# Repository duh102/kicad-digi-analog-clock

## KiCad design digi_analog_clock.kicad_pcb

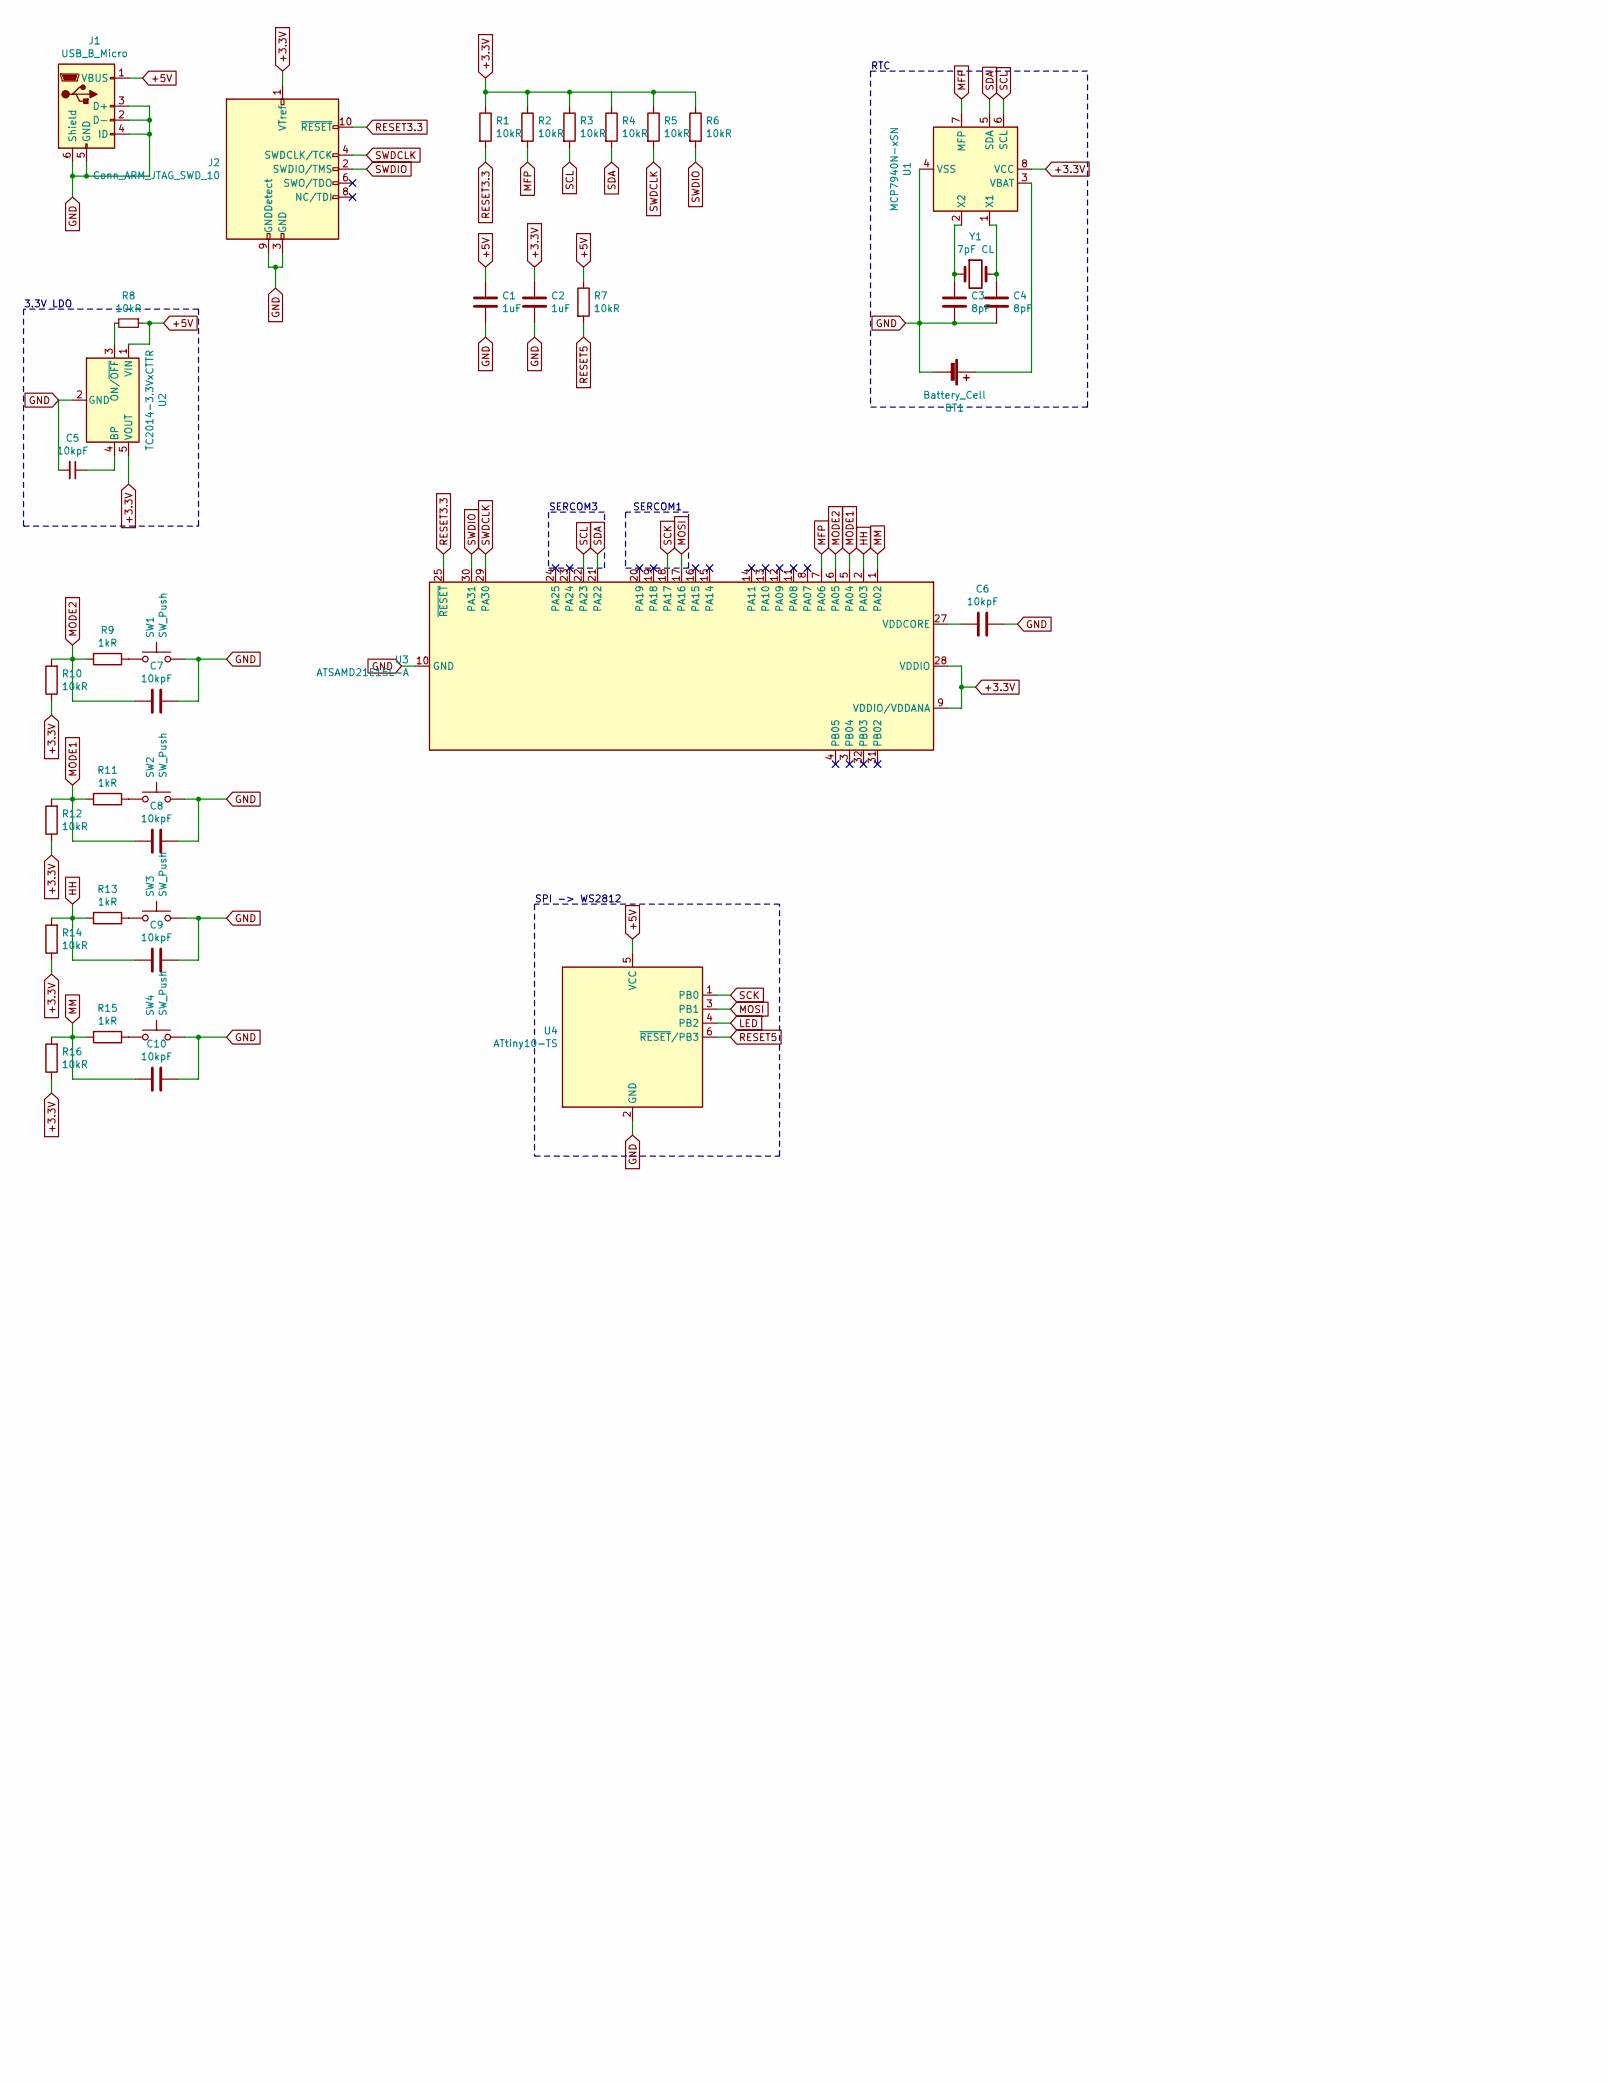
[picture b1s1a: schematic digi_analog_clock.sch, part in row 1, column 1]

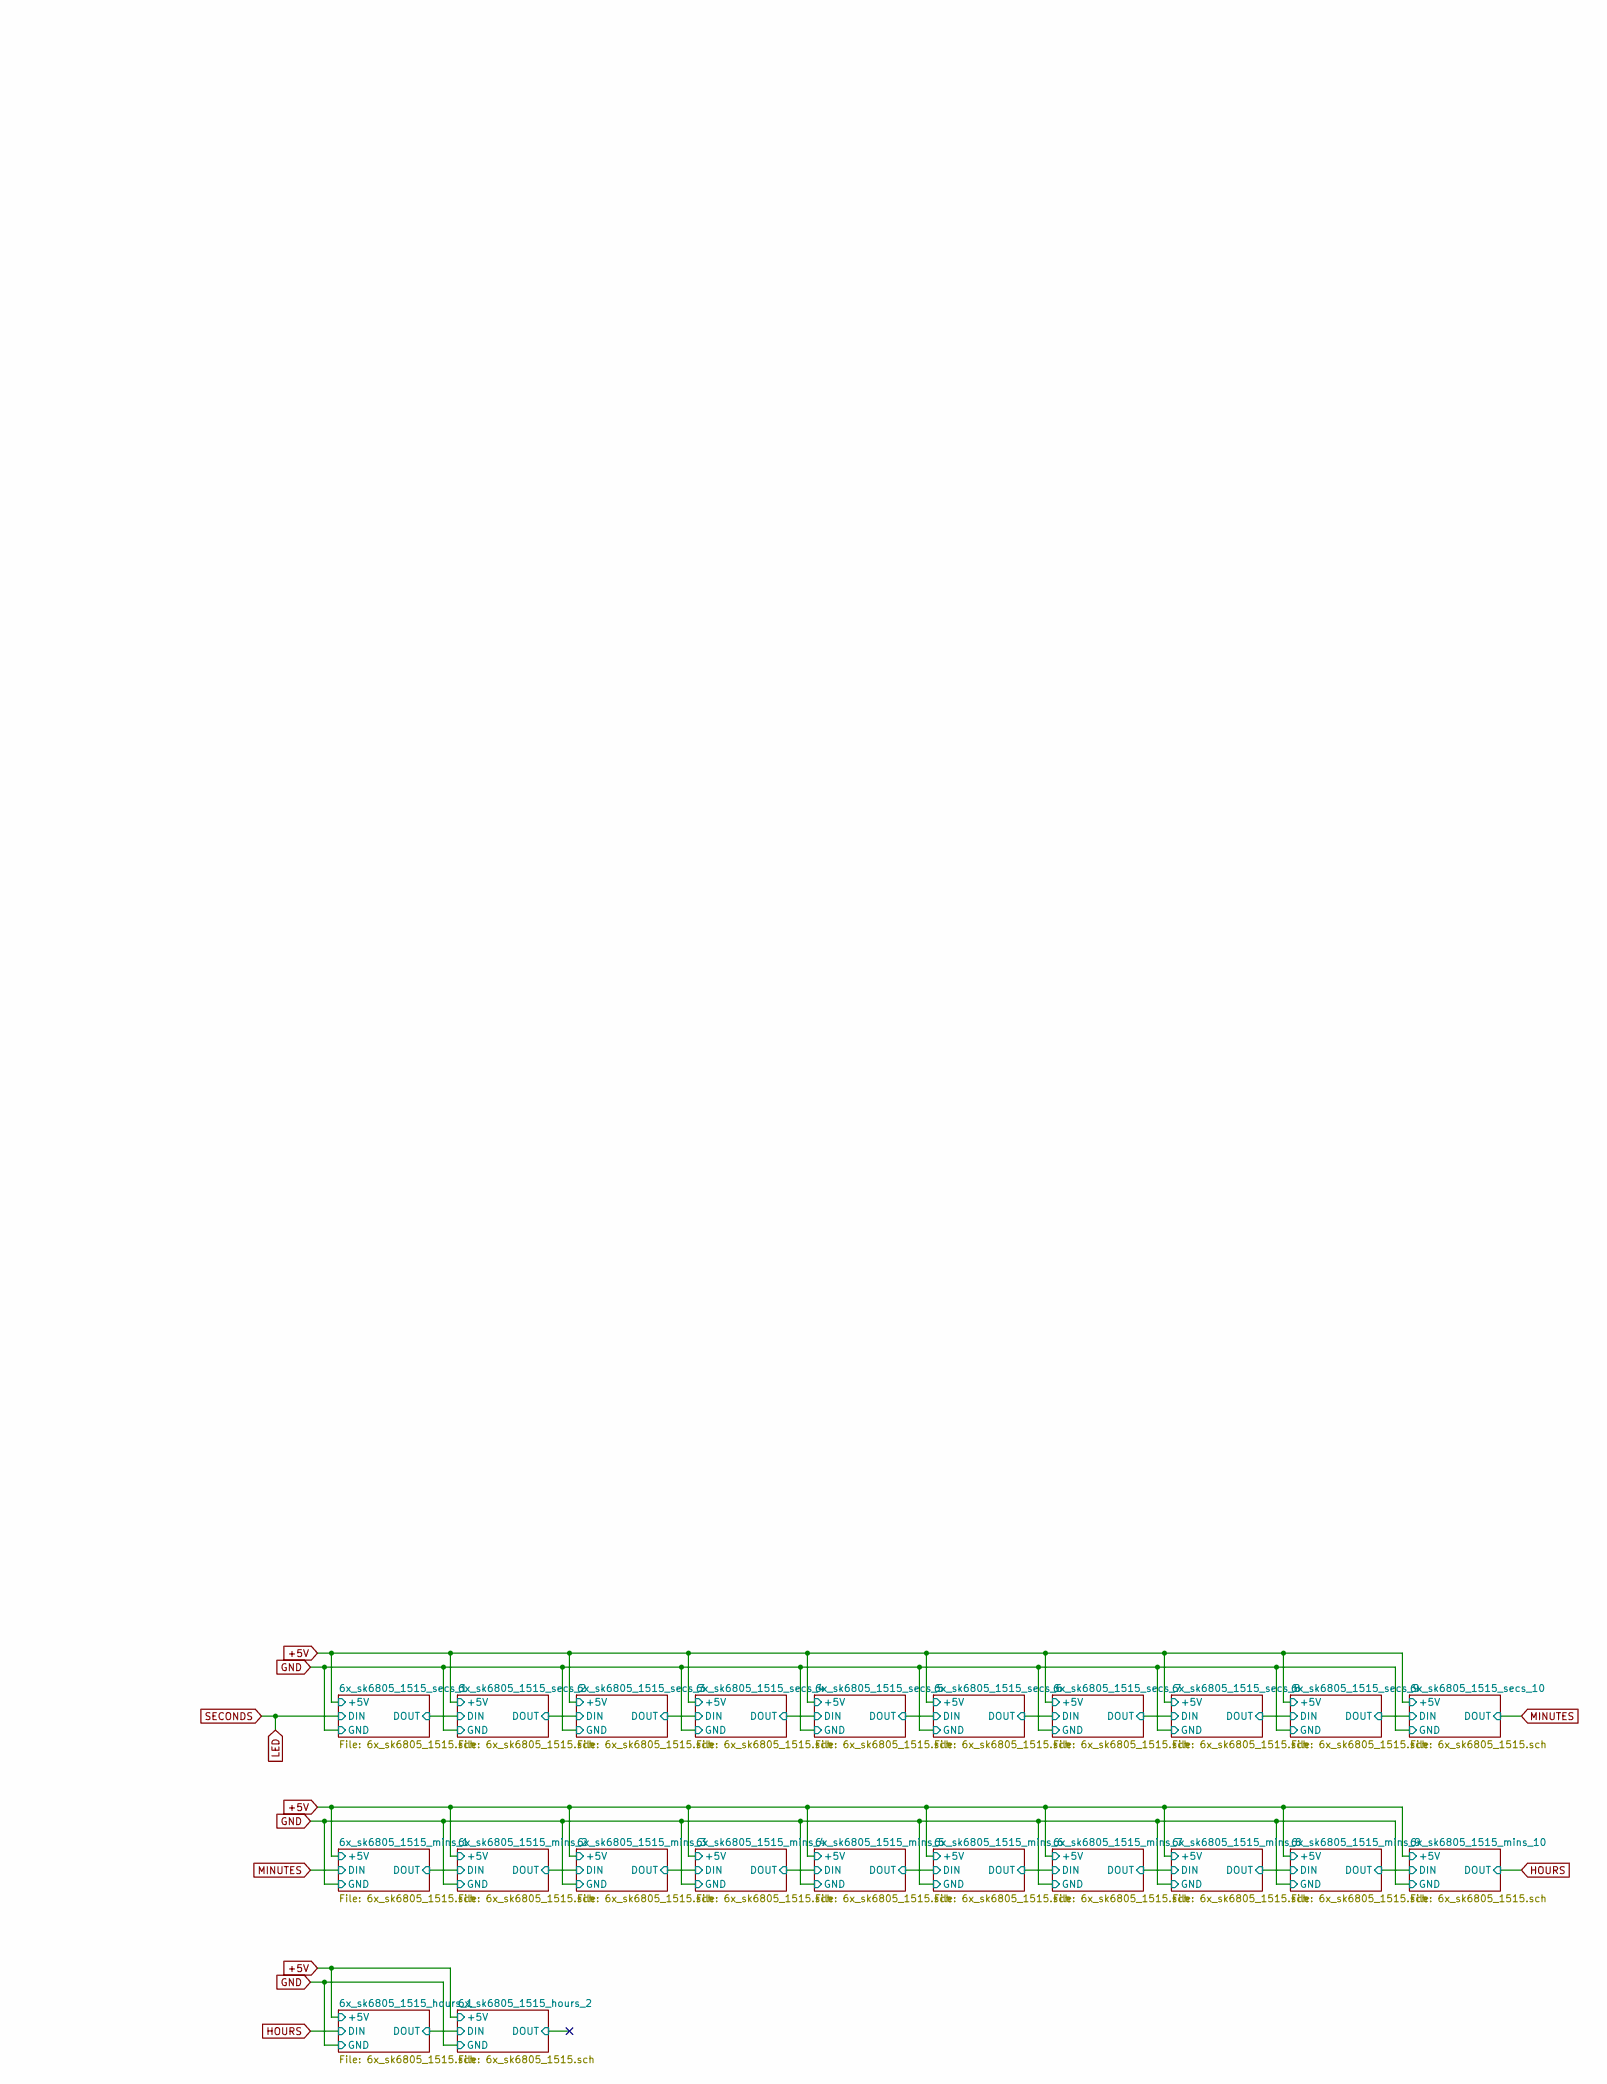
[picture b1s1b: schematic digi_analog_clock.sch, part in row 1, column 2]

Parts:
BT1: Battery_Cell; BatteryHolder_Keystone_3034_1x20mm
C1, C2: 1uF; C_0805_2012Metric
C3, C4: 8pF; C_0805_2012Metric
C5, C6, C7, C8, C9, C10: 10kpF; C_0603_1608Metric
J1: USB_B_Micro; USB_Micro_B_Female_10118194-0001LF
J2: Conn_ARM_JTAG_SWD_10; PinHeader_2x05_P1.27mm_Vertical_SMD
R1, R2, R3, R4, R5, R6, R7, R8, R10, R12, R14, R16: 10kR; R_0805_2012Metric
R9, R11, R13, R15: 1kR; R_0805_2012Metric
SW1, SW2, SW3, SW4: SW_Push; SW_Push_1P1T_Vertical_CK_PTS815
U1: MCP7940N-xSN; SOIC-8_3.9x4.9mm_P1.27mm
U2: TC2014-3.3VxCTTR; SOT-23-5
U3: ATSAMD21E15L-A; TQFP-32_7x7mm_P0.8mm
U4: ATtiny10-TS; SOT-23-6
Y1: 7pF CL; Crystal_SMD_G8-2Pin_3.2x1.5mm

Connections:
+3.3V: C2.1, J2.1 (VTref), R1.1, R2.1, R3.1, R4.1, R5.1, R6.1, R10.1, R12.1, R14.1, R16.1, U1.8 (VCC), U2.5 (VOUT), U3.9 (VDDIO/VDDANA), U3.28 (VDDIO)
+5V: C1.1, J1.1 (VBUS), R7.1, R8.1, U2.1 (VIN), U4.5 (VCC); also elsewhere on the board
GND: BT1.2 (-), C1.2, C2.2, C3.2, C4.1, C5.2, C6.1, C7.1, C8.1, C9.1, C10.1, J1.2 (D-), J1.3 (D+), J1.4 (ID), J1.5 (GND), J1.6 (Shield), J2.3 (GND), J2.5 (GND), J2.9 (GNDDetect), SW1.2, SW2.2, SW3.2, SW4.2, U1.4 (VSS), U2.2 (GND), U3.10 (GND), U3.26 (GND), U4.2 (GND); also elsewhere on the board
HH: C9.2, R13.2, R14.2, U3.2 (PA03)
LED: U4.4 (PB2); also elsewhere on the board
MFP: R2.2, U1.7 (MFP), U3.7 (PA06)
MM: C10.2, R15.2, R16.2, U3.1 (PA02)
MODE1: C8.2, R11.2, R12.2, U3.5 (PA04)
MODE2: C7.2, R9.2, R10.2, U3.6 (PA05)
MOSI: U3.17 (PA16), U4.3 (PB1)
unnamed: BT1.1 (+), U1.3 (VBAT)
unnamed: C3.1, U1.2 (X2), Y1.1
unnamed: C4.2, U1.1 (X1), Y1.2
unnamed: C5.1, U2.4 (BP)
unnamed: C6.2, U3.27 (VDDCORE)
unnamed: R8.2, U2.3 (ON/~OFF~)
unnamed 147: R9.1, SW1.1; also elsewhere on the board
unnamed 148: R11.1, SW2.1; also elsewhere on the board
unnamed 149: R13.1, SW3.1; also elsewhere on the board
unnamed 150: R15.1, SW4.1; also elsewhere on the board
RESET3.3: J2.10 (~RESET~), R1.2, U3.25 (~RESET)
RESET5: R7.2, U4.6 (~RESET~/PB3)
SCK: U3.18 (PA17), U4.1 (PB0)
SCL: R3.2, U1.6 (SCL), U3.22 (PA23)
SDA: R4.2, U1.5 (SDA), U3.21 (PA22)
SWDCLK: J2.4 (SWDCLK/TCK), R5.2, U3.29 (PA30)
SWDIO: J2.2 (SWDIO/TMS), R6.2, U3.30 (PA31)

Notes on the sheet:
SERCOM1
SERCOM3
RTC
SPI -> WS2812
3.3V LDO

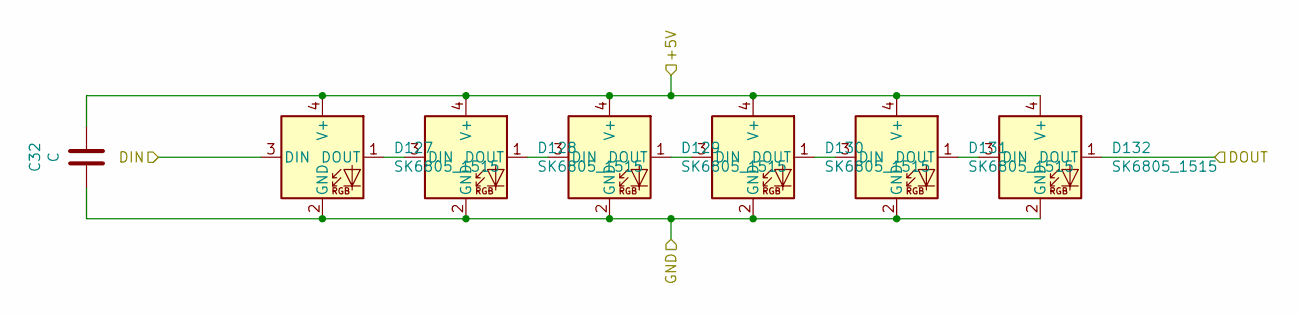
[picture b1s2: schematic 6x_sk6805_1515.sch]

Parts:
C21: C; C_0603_1608Metric
D61, D62, D63, D64, D65, D66: SK6805_1515; LED_SK6805_PLCC4_1.5x1.5mm_P0.65mm

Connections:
+5V: C21.1, D61.4 (V+), D62.4 (V+), D63.4 (V+), D64.4 (V+), D65.4 (V+), D66.4 (V+); also elsewhere on the board
/6x_sk6805_1515_mins_2/DIN: D66.1 (DOUT); also elsewhere on the board
GND: C21.2, D61.2 (GND), D62.2 (GND), D63.2 (GND), D64.2 (GND), D65.2 (GND), D66.2 (GND); also elsewhere on the board
MINUTES: D61.3 (DIN); also elsewhere on the board
unnamed: D61.1 (DOUT), D62.3 (DIN)
unnamed: D62.1 (DOUT), D63.3 (DIN)
unnamed: D63.1 (DOUT), D64.3 (DIN)
unnamed: D64.1 (DOUT), D65.3 (DIN)
unnamed: D65.1 (DOUT), D66.3 (DIN)

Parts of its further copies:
C11, C12, C13, C14, C15, C16, C17, C18, C19, C20, C22, C23, C24, C25, C26, C27, C28, C29, C30, C31, C32: C; C_0603_1608Metric
D1, D2, D3, D4, D5, D6, D7, D8, D9, D10, D11, D12, D13, D14, D15, D16, D17, D18, D19, D20, D21, D22, D23, D24, D25, D26, D27, D28, D29, D30, D31, D32, D33, D34, D35, D36, D37, D38, D39, D40, D41, D42, D43, D44, D45, D46, D47, D48, D49, D50, D51, D52, D53, D54, D55, D56, D57, D58, D59, D60, D67, D68, D69, D70, D71, D72, D73, D74, D75, D76, D77, D78, D79, D80, D81, D82, D83, D84, D85, D86, D87, D88, D89, D90, D91, D92, D93, D94, D95, D96, D97, D98, D99, D100, D101, D102, D103, D104, D105, D106, D107, D108, D109, D110, D111, D112, D113, D114, D115, D116, D117, D118, D119, D120, D121, D122, D123, D124, D125, D126, D127, D128, D129, D130, D131, D132: SK6805_1515; LED_SK6805_PLCC4_1.5x1.5mm_P0.65mm

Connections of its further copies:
+5V: C11.1, C12.1, C13.1, C14.1, C15.1, C16.1, C17.1, C18.1, C19.1, C20.1, C22.1, C23.1, C24.1, C25.1, C26.1, C27.1, C28.1, C29.1, C30.1, C31.1, C32.1, D1.4 (V+), D2.4 (V+), D3.4 (V+), D4.4 (V+), D5.4 (V+), D6.4 (V+), D7.4 (V+), D8.4 (V+), D9.4 (V+), D10.4 (V+), D11.4 (V+), D12.4 (V+), D13.4 (V+), D14.4 (V+), D15.4 (V+), D16.4 (V+), D17.4 (V+), D18.4 (V+), D19.4 (V+), D20.4 (V+), D21.4 (V+), D22.4 (V+), D23.4 (V+), D24.4 (V+), D25.4 (V+), D26.4 (V+), D27.4 (V+), D28.4 (V+), D29.4 (V+), D30.4 (V+), D31.4 (V+), D32.4 (V+), D33.4 (V+), D34.4 (V+), D35.4 (V+), D36.4 (V+), D37.4 (V+), D38.4 (V+), D39.4 (V+), D40.4 (V+), D41.4 (V+), D42.4 (V+), D43.4 (V+), D44.4 (V+), D45.4 (V+), D46.4 (V+), D47.4 (V+), D48.4 (V+), D49.4 (V+), D50.4 (V+), D51.4 (V+), D52.4 (V+), D53.4 (V+), D54.4 (V+), D55.4 (V+), D56.4 (V+), D57.4 (V+), D58.4 (V+), D59.4 (V+), D60.4 (V+), D67.4 (V+), D68.4 (V+), D69.4 (V+), D70.4 (V+), D71.4 (V+), D72.4 (V+), D73.4 (V+), D74.4 (V+), D75.4 (V+), D76.4 (V+), D77.4 (V+), D78.4 (V+), D79.4 (V+), D80.4 (V+), D81.4 (V+), D82.4 (V+), D83.4 (V+), D84.4 (V+), D85.4 (V+), D86.4 (V+), D87.4 (V+), D88.4 (V+), D89.4 (V+), D90.4 (V+), D91.4 (V+), D92.4 (V+), D93.4 (V+), D94.4 (V+), D95.4 (V+), D96.4 (V+), D97.4 (V+), D98.4 (V+), D99.4 (V+), D100.4 (V+), D101.4 (V+), D102.4 (V+), D103.4 (V+), D104.4 (V+), D105.4 (V+), D106.4 (V+), D107.4 (V+), D108.4 (V+), D109.4 (V+), D110.4 (V+), D111.4 (V+), D112.4 (V+), D113.4 (V+), D114.4 (V+), D115.4 (V+), D116.4 (V+), D117.4 (V+), D118.4 (V+), D119.4 (V+), D120.4 (V+), D121.4 (V+), D122.4 (V+), D123.4 (V+), D124.4 (V+), D125.4 (V+), D126.4 (V+), D127.4 (V+), D128.4 (V+), D129.4 (V+), D130.4 (V+), D131.4 (V+), D132.4 (V+); also elsewhere on the board
/6x_sk6805_1515_hours_2/DIN: D126.1 (DOUT), D127.3 (DIN)
/6x_sk6805_1515_mins_2/DIN: D67.3 (DIN); also elsewhere on the board
/6x_sk6805_1515_mins_3/DIN: D72.1 (DOUT), D73.3 (DIN)
/6x_sk6805_1515_mins_4/DIN: D78.1 (DOUT), D79.3 (DIN)
/6x_sk6805_1515_mins_5/DIN: D84.1 (DOUT), D85.3 (DIN)
/6x_sk6805_1515_mins_6/DIN: D90.1 (DOUT), D91.3 (DIN)
/6x_sk6805_1515_mins_7/DIN: D96.1 (DOUT), D97.3 (DIN)
/6x_sk6805_1515_mins_8/DIN: D102.1 (DOUT), D103.3 (DIN)
/6x_sk6805_1515_mins_9/DIN: D108.1 (DOUT), D109.3 (DIN)
/6x_sk6805_1515_mins_10/DIN: D114.1 (DOUT), D115.3 (DIN)
/6x_sk6805_1515_secs_2/DIN: D6.1 (DOUT), D7.3 (DIN)
/6x_sk6805_1515_secs_3/DIN: D12.1 (DOUT), D13.3 (DIN)
/6x_sk6805_1515_secs_4/DIN: D18.1 (DOUT), D19.3 (DIN)
/6x_sk6805_1515_secs_5/DIN: D24.1 (DOUT), D25.3 (DIN)
/6x_sk6805_1515_secs_6/DIN: D30.1 (DOUT), D31.3 (DIN)
/6x_sk6805_1515_secs_7/DIN: D36.1 (DOUT), D37.3 (DIN)
/6x_sk6805_1515_secs_8/DIN: D42.1 (DOUT), D43.3 (DIN)
/6x_sk6805_1515_secs_9/DIN: D48.1 (DOUT), D49.3 (DIN)
/6x_sk6805_1515_secs_10/DIN: D54.1 (DOUT), D55.3 (DIN)
GND: C11.2, C12.2, C13.2, C14.2, C15.2, C16.2, C17.2, C18.2, C19.2, C20.2, C22.2, C23.2, C24.2, C25.2, C26.2, C27.2, C28.2, C29.2, C30.2, C31.2, C32.2, D1.2 (GND), D2.2 (GND), D3.2 (GND), D4.2 (GND), D5.2 (GND), D6.2 (GND), D7.2 (GND), D8.2 (GND), D9.2 (GND), D10.2 (GND), D11.2 (GND), D12.2 (GND), D13.2 (GND), D14.2 (GND), D15.2 (GND), D16.2 (GND), D17.2 (GND), D18.2 (GND), D19.2 (GND), D20.2 (GND), D21.2 (GND), D22.2 (GND), D23.2 (GND), D24.2 (GND), D25.2 (GND), D26.2 (GND), D27.2 (GND), D28.2 (GND), D29.2 (GND), D30.2 (GND), D31.2 (GND), D32.2 (GND), D33.2 (GND), D34.2 (GND), D35.2 (GND), D36.2 (GND), D37.2 (GND), D38.2 (GND), D39.2 (GND), D40.2 (GND), D41.2 (GND), D42.2 (GND), D43.2 (GND), D44.2 (GND), D45.2 (GND), D46.2 (GND), D47.2 (GND), D48.2 (GND), D49.2 (GND), D50.2 (GND), D51.2 (GND), D52.2 (GND), D53.2 (GND), D54.2 (GND), D55.2 (GND), D56.2 (GND), D57.2 (GND), D58.2 (GND), D59.2 (GND), D60.2 (GND), D67.2 (GND), D68.2 (GND), D69.2 (GND), D70.2 (GND), D71.2 (GND), D72.2 (GND), D73.2 (GND), D74.2 (GND), D75.2 (GND), D76.2 (GND), D77.2 (GND), D78.2 (GND), D79.2 (GND), D80.2 (GND), D81.2 (GND), D82.2 (GND), D83.2 (GND), D84.2 (GND), D85.2 (GND), D86.2 (GND), D87.2 (GND), D88.2 (GND), D89.2 (GND), D90.2 (GND), D91.2 (GND), D92.2 (GND), D93.2 (GND), D94.2 (GND), D95.2 (GND), D96.2 (GND), D97.2 (GND), D98.2 (GND), D99.2 (GND), D100.2 (GND), D101.2 (GND), D102.2 (GND), D103.2 (GND), D104.2 (GND), D105.2 (GND), D106.2 (GND), D107.2 (GND), D108.2 (GND), D109.2 (GND), D110.2 (GND), D111.2 (GND), D112.2 (GND), D113.2 (GND), D114.2 (GND), D115.2 (GND), D116.2 (GND), D117.2 (GND), D118.2 (GND), D119.2 (GND), D120.2 (GND), D121.2 (GND), D122.2 (GND), D123.2 (GND), D124.2 (GND), D125.2 (GND), D126.2 (GND), D127.2 (GND), D128.2 (GND), D129.2 (GND), D130.2 (GND), D131.2 (GND), D132.2 (GND); also elsewhere on the board
HOURS: D120.1 (DOUT), D121.3 (DIN)
LED: D1.3 (DIN); also elsewhere on the board
MINUTES: D60.1 (DOUT); also elsewhere on the board
unnamed: D1.1 (DOUT), D2.3 (DIN)
unnamed: D2.1 (DOUT), D3.3 (DIN)
unnamed: D3.1 (DOUT), D4.3 (DIN)
unnamed: D4.1 (DOUT), D5.3 (DIN)
unnamed: D5.1 (DOUT), D6.3 (DIN)
unnamed: D7.1 (DOUT), D8.3 (DIN)
unnamed: D8.1 (DOUT), D9.3 (DIN)
unnamed: D10.1 (DOUT), D11.3 (DIN)
unnamed: D9.1 (DOUT), D10.3 (DIN)
unnamed: D11.1 (DOUT), D12.3 (DIN)
unnamed: D13.1 (DOUT), D14.3 (DIN)
unnamed: D14.1 (DOUT), D15.3 (DIN)
unnamed: D15.1 (DOUT), D16.3 (DIN)
unnamed: D16.1 (DOUT), D17.3 (DIN)
unnamed: D17.1 (DOUT), D18.3 (DIN)
unnamed: D19.1 (DOUT), D20.3 (DIN)
unnamed: D20.1 (DOUT), D21.3 (DIN)
unnamed: D21.1 (DOUT), D22.3 (DIN)
unnamed: D22.1 (DOUT), D23.3 (DIN)
unnamed: D23.1 (DOUT), D24.3 (DIN)
unnamed: D25.1 (DOUT), D26.3 (DIN)
unnamed: D26.1 (DOUT), D27.3 (DIN)
unnamed: D27.1 (DOUT), D28.3 (DIN)
unnamed: D28.1 (DOUT), D29.3 (DIN)
unnamed: D29.1 (DOUT), D30.3 (DIN)
unnamed: D31.1 (DOUT), D32.3 (DIN)
unnamed: D32.1 (DOUT), D33.3 (DIN)
unnamed: D33.1 (DOUT), D34.3 (DIN)
unnamed: D34.1 (DOUT), D35.3 (DIN)
unnamed: D35.1 (DOUT), D36.3 (DIN)
unnamed: D37.1 (DOUT), D38.3 (DIN)
unnamed: D38.1 (DOUT), D39.3 (DIN)
unnamed: D39.1 (DOUT), D40.3 (DIN)
unnamed: D40.1 (DOUT), D41.3 (DIN)
unnamed: D41.1 (DOUT), D42.3 (DIN)
unnamed: D43.1 (DOUT), D44.3 (DIN)
unnamed: D44.1 (DOUT), D45.3 (DIN)
unnamed: D45.1 (DOUT), D46.3 (DIN)
unnamed: D46.1 (DOUT), D47.3 (DIN)
unnamed: D47.1 (DOUT), D48.3 (DIN)
unnamed: D49.1 (DOUT), D50.3 (DIN)
unnamed: D50.1 (DOUT), D51.3 (DIN)
unnamed: D51.1 (DOUT), D52.3 (DIN)
unnamed: D52.1 (DOUT), D53.3 (DIN)
unnamed: D53.1 (DOUT), D54.3 (DIN)
unnamed: D55.1 (DOUT), D56.3 (DIN)
unnamed: D56.1 (DOUT), D57.3 (DIN)
unnamed: D57.1 (DOUT), D58.3 (DIN)
unnamed: D58.1 (DOUT), D59.3 (DIN)
unnamed: D59.1 (DOUT), D60.3 (DIN)
unnamed: D67.1 (DOUT), D68.3 (DIN)
unnamed: D68.1 (DOUT), D69.3 (DIN)
unnamed: D69.1 (DOUT), D70.3 (DIN)
unnamed: D70.1 (DOUT), D71.3 (DIN)
unnamed: D71.1 (DOUT), D72.3 (DIN)
unnamed: D73.1 (DOUT), D74.3 (DIN)
unnamed: D74.1 (DOUT), D75.3 (DIN)
unnamed: D75.1 (DOUT), D76.3 (DIN)
unnamed: D76.1 (DOUT), D77.3 (DIN)
unnamed: D77.1 (DOUT), D78.3 (DIN)
unnamed: D79.1 (DOUT), D80.3 (DIN)
unnamed: D80.1 (DOUT), D81.3 (DIN)
unnamed: D81.1 (DOUT), D82.3 (DIN)
unnamed: D82.1 (DOUT), D83.3 (DIN)
unnamed: D83.1 (DOUT), D84.3 (DIN)
unnamed: D85.1 (DOUT), D86.3 (DIN)
unnamed: D86.1 (DOUT), D87.3 (DIN)
unnamed: D87.1 (DOUT), D88.3 (DIN)
unnamed: D88.1 (DOUT), D89.3 (DIN)
unnamed: D89.1 (DOUT), D90.3 (DIN)
unnamed: D91.1 (DOUT), D92.3 (DIN)
unnamed: D92.1 (DOUT), D93.3 (DIN)
unnamed: D93.1 (DOUT), D94.3 (DIN)
unnamed: D94.1 (DOUT), D95.3 (DIN)
unnamed: D95.1 (DOUT), D96.3 (DIN)
unnamed: D97.1 (DOUT), D98.3 (DIN)
unnamed: D98.1 (DOUT), D99.3 (DIN)
unnamed: D100.1 (DOUT), D101.3 (DIN)
unnamed: D99.1 (DOUT), D100.3 (DIN)
unnamed: D101.1 (DOUT), D102.3 (DIN)
unnamed: D103.1 (DOUT), D104.3 (DIN)
unnamed: D104.1 (DOUT), D105.3 (DIN)
unnamed: D105.1 (DOUT), D106.3 (DIN)
unnamed: D106.1 (DOUT), D107.3 (DIN)
unnamed: D107.1 (DOUT), D108.3 (DIN)
unnamed: D109.1 (DOUT), D110.3 (DIN)
unnamed: D110.1 (DOUT), D111.3 (DIN)
unnamed: D111.1 (DOUT), D112.3 (DIN)
unnamed: D112.1 (DOUT), D113.3 (DIN)
unnamed: D113.1 (DOUT), D114.3 (DIN)
unnamed: D115.1 (DOUT), D116.3 (DIN)
unnamed: D116.1 (DOUT), D117.3 (DIN)
unnamed: D117.1 (DOUT), D118.3 (DIN)
unnamed: D118.1 (DOUT), D119.3 (DIN)
unnamed: D119.1 (DOUT), D120.3 (DIN)
unnamed: D121.1 (DOUT), D122.3 (DIN)
unnamed: D122.1 (DOUT), D123.3 (DIN)
unnamed: D123.1 (DOUT), D124.3 (DIN)
unnamed: D124.1 (DOUT), D125.3 (DIN)
unnamed: D125.1 (DOUT), D126.3 (DIN)
unnamed: D127.1 (DOUT), D128.3 (DIN)
unnamed: D128.1 (DOUT), D129.3 (DIN)
unnamed: D129.1 (DOUT), D130.3 (DIN)
unnamed: D130.1 (DOUT), D131.3 (DIN)
unnamed: D131.1 (DOUT), D132.3 (DIN)

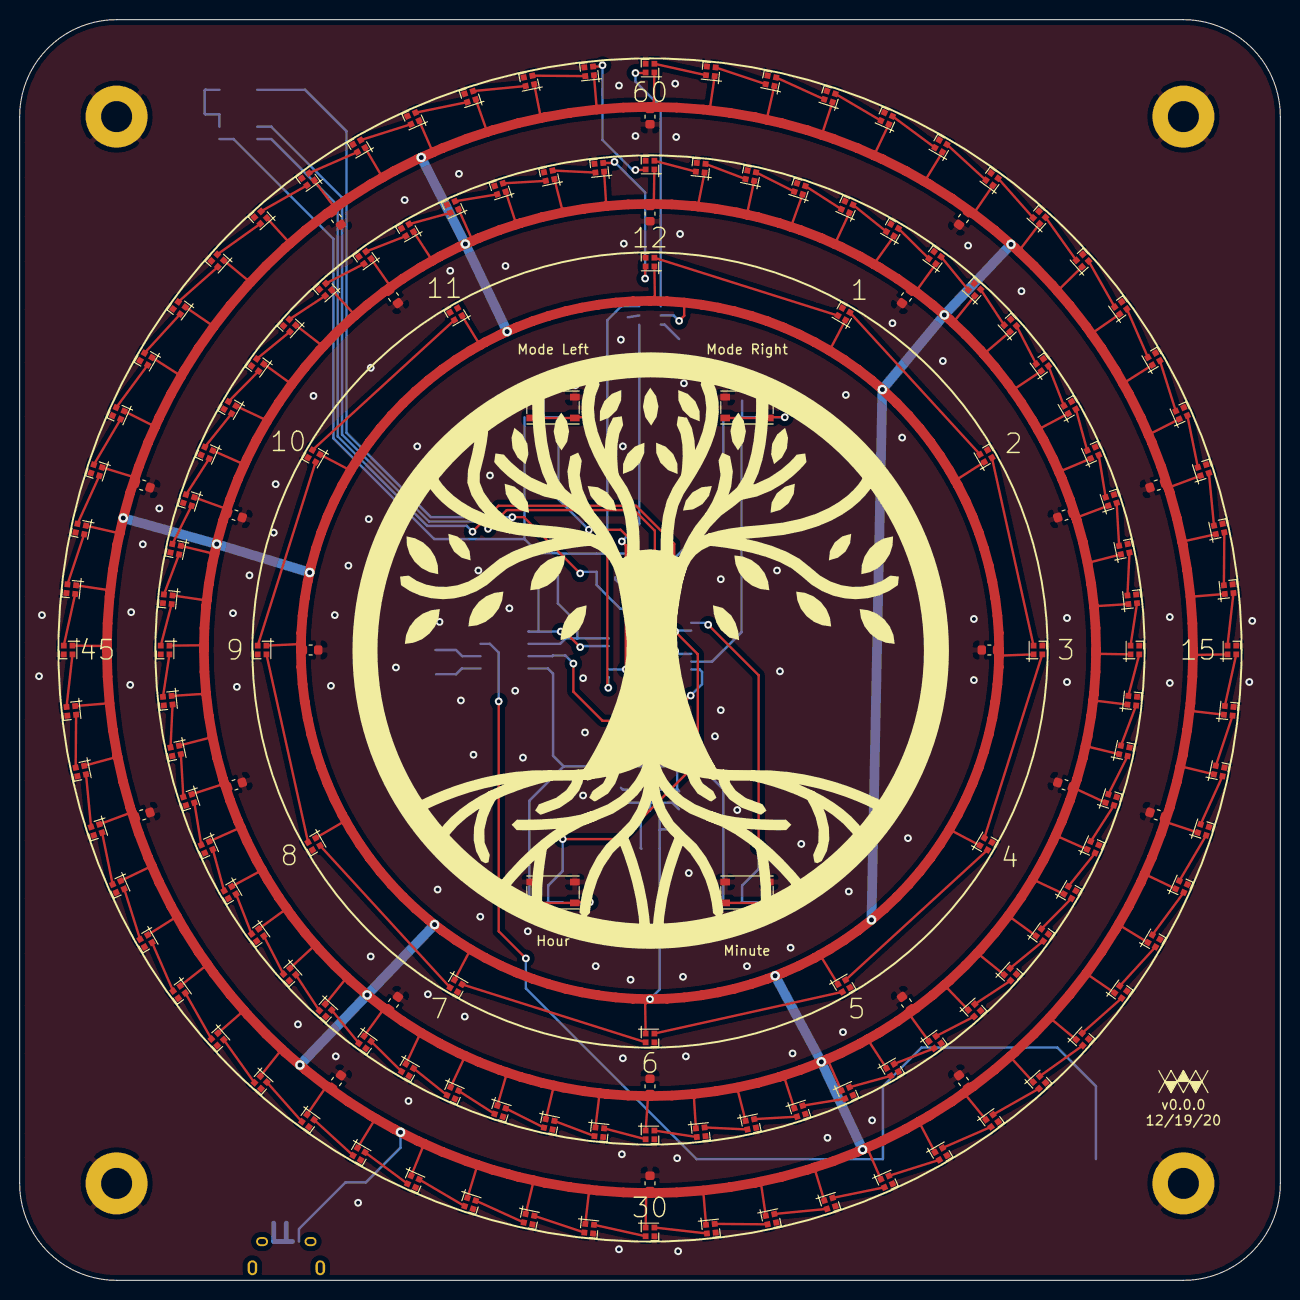
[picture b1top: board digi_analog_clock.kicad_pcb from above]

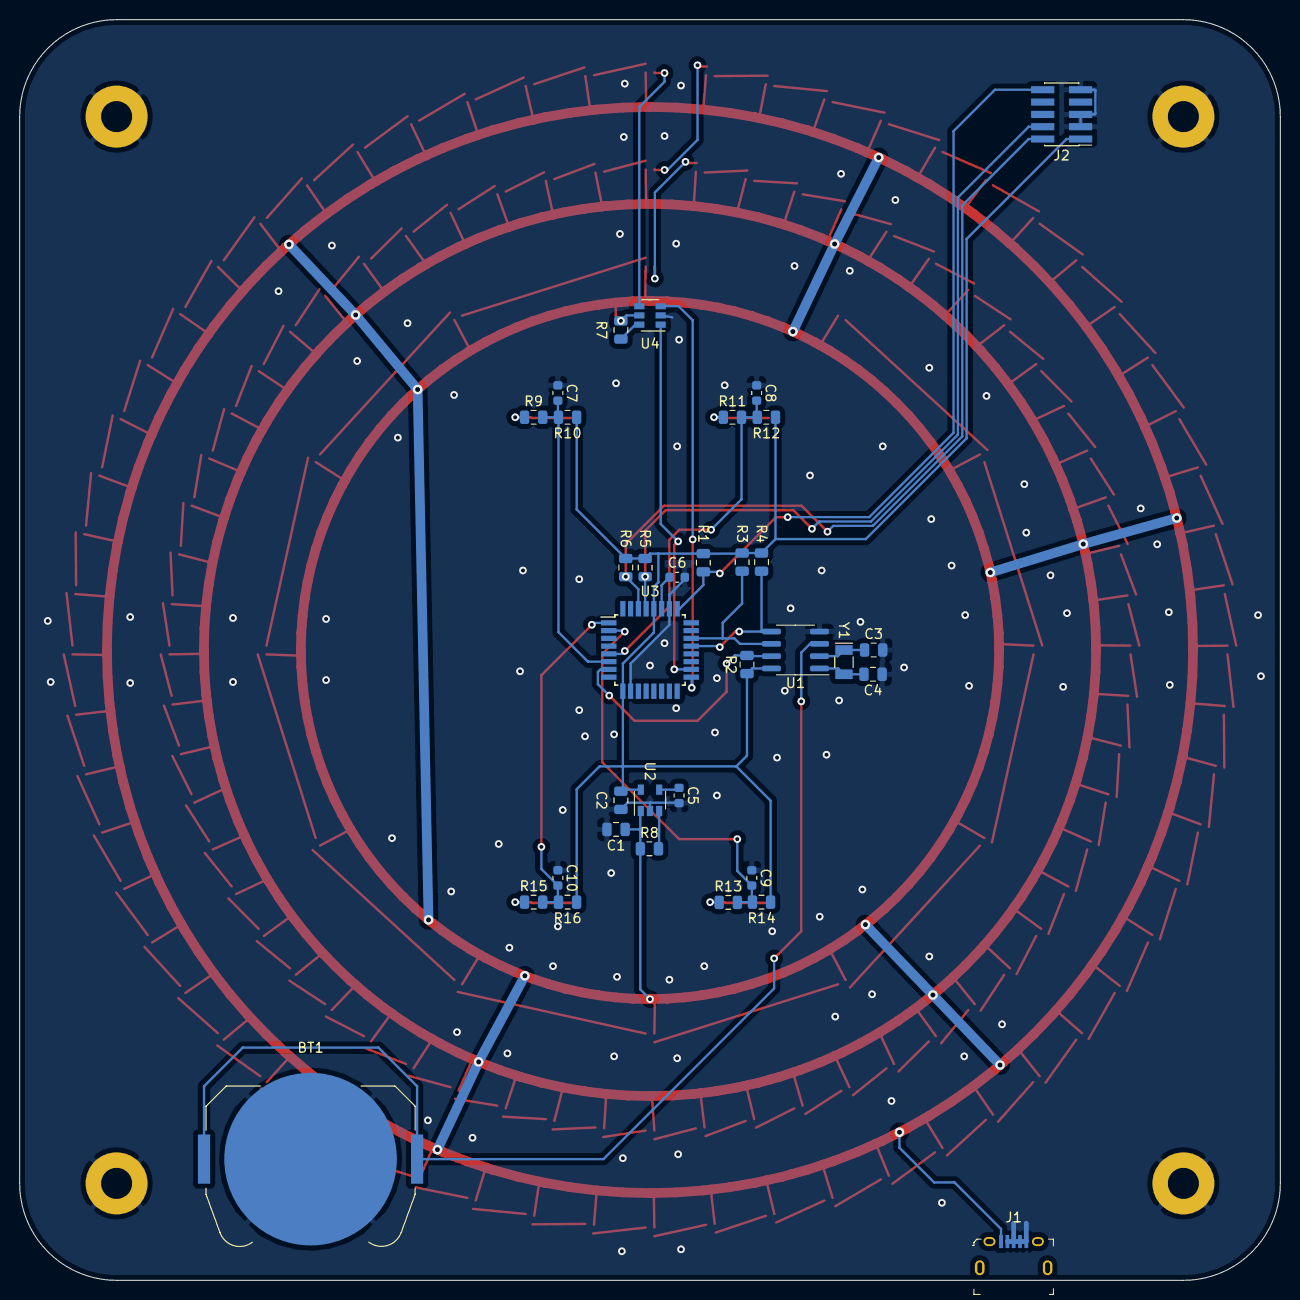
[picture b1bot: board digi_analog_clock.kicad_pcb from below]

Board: 2 copper layers, 130.0 x 130.0 mm, 192 parts (34 on the bottom side), 158 nets.

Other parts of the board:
Hour: SW_Push; SW_Push_1P1T_Vertical_CK_PTS815
Minute: SW_Push; SW_Push_1P1T_Vertical_CK_PTS815
Mode Left: SW_Push; SW_Push_1P1T_Vertical_CK_PTS815
Mode Right: SW_Push; SW_Push_1P1T_Vertical_CK_PTS815

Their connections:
GND: Hour.2, Minute.2, Mode Left.2, Mode Right.2; also elsewhere on the board
unnamed 147: Mode Right.1; also elsewhere on the board
unnamed 148: Mode Left.1; also elsewhere on the board
unnamed 149: Hour.1; also elsewhere on the board
unnamed 150: Minute.1; also elsewhere on the board

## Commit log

2020-01-19 Nailed down clock circuit
2020-02-08 Add sk6805 blocks
2020-12-09 Some updates, not finished
2020-12-19 Use atsamd21; do most layout
2020-12-20 Add yggdrasil art; plot

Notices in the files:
parts and their libraries:
Copyright Ery Prihananto eryprihananto@gmail.com
